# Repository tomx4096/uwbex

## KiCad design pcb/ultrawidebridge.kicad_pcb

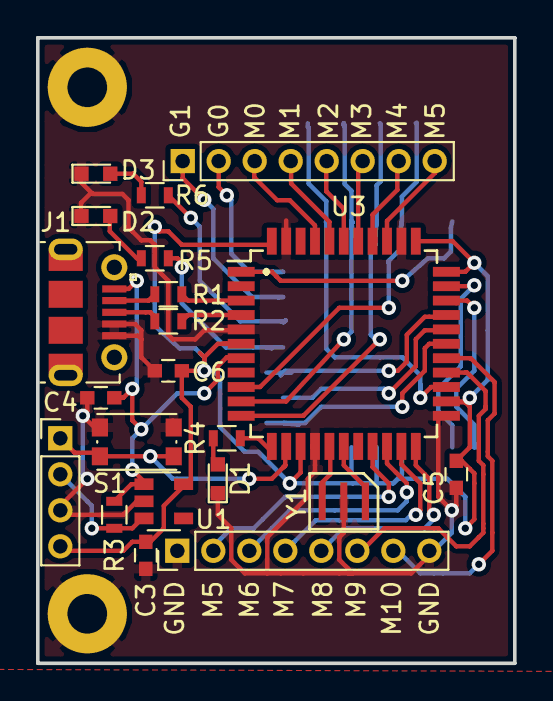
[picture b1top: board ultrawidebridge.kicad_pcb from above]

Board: 2 copper layers, 26.5 x 34.8 mm, 19 parts (1 on the bottom side), 27 nets.

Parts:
C3, C4, C5: 10uF; C_0603
C6: 1uF; C_0603
D1, D2, D3: LED; LED_0603
J1: USB_A; USB_Micro-B_Molex-105017-0001
R1, R2: 22; R_0603
R3: 100k; R_0603
R4: 2.2K; R_0603
R5, R6: 330; R_0603
S1: CONN_01X04; spst_kmr2
U1: SPX3819-3.3; SOT23-5
U2: DWM1000; dwm1000
U3: ATMEGA32U4-MU; TQFP-44_10x10mm_Pitch0.8mm
Y1: Resonator; smd_resonator_cstce_g15c

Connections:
+3V3: C3.1, C5.1, C6.1, U1.5, U2.5, U2.6, U2.7, U3.6, U3.14, U3.24, U3.33, U3.34, U3.44
/CLK: U2.20, U3.9
/CSn: U2.17, U3.25
/EN: R3.1, U1.3
/INTq: U2.22, U3.1
/MISO: U2.19, U3.11
/MOSI: U2.18, U3.10
/RST: S1.1, U3.13
/VBUS: C4.1, J1.1, R3.2, U1.1, U3.7
/WAKE: U2.2, U3.31
/g4: U2.11, U3.30
/g5: U2.10, U3.29
/g6: U2.9, U3.28
/gRST: U2.3, U3.32
GND: C3.2, C4.2, C5.2, C6.2, D1.1, D2.1, D3.1, J1.4, J1.5, S1.2, U1.2, U2.8, U2.16, U2.21, U2.23, U2.24, U3.5, U3.15, U3.23, U3.35, U3.43, Y1.2
unnamed: D1.2, R4.1
unnamed: D2.2, R5.2
unnamed: D3.2, R6.2
unnamed: J1.2, R1.2
unnamed: J1.3, R2.2
unnamed: R1.1, U3.3
unnamed: R2.1, U3.4
unnamed: R4.2, U3.12
unnamed: R5.1, U2.12
unnamed: R6.1, U2.13
unnamed: U3.16, Y1.3
unnamed: U3.17, Y1.1
